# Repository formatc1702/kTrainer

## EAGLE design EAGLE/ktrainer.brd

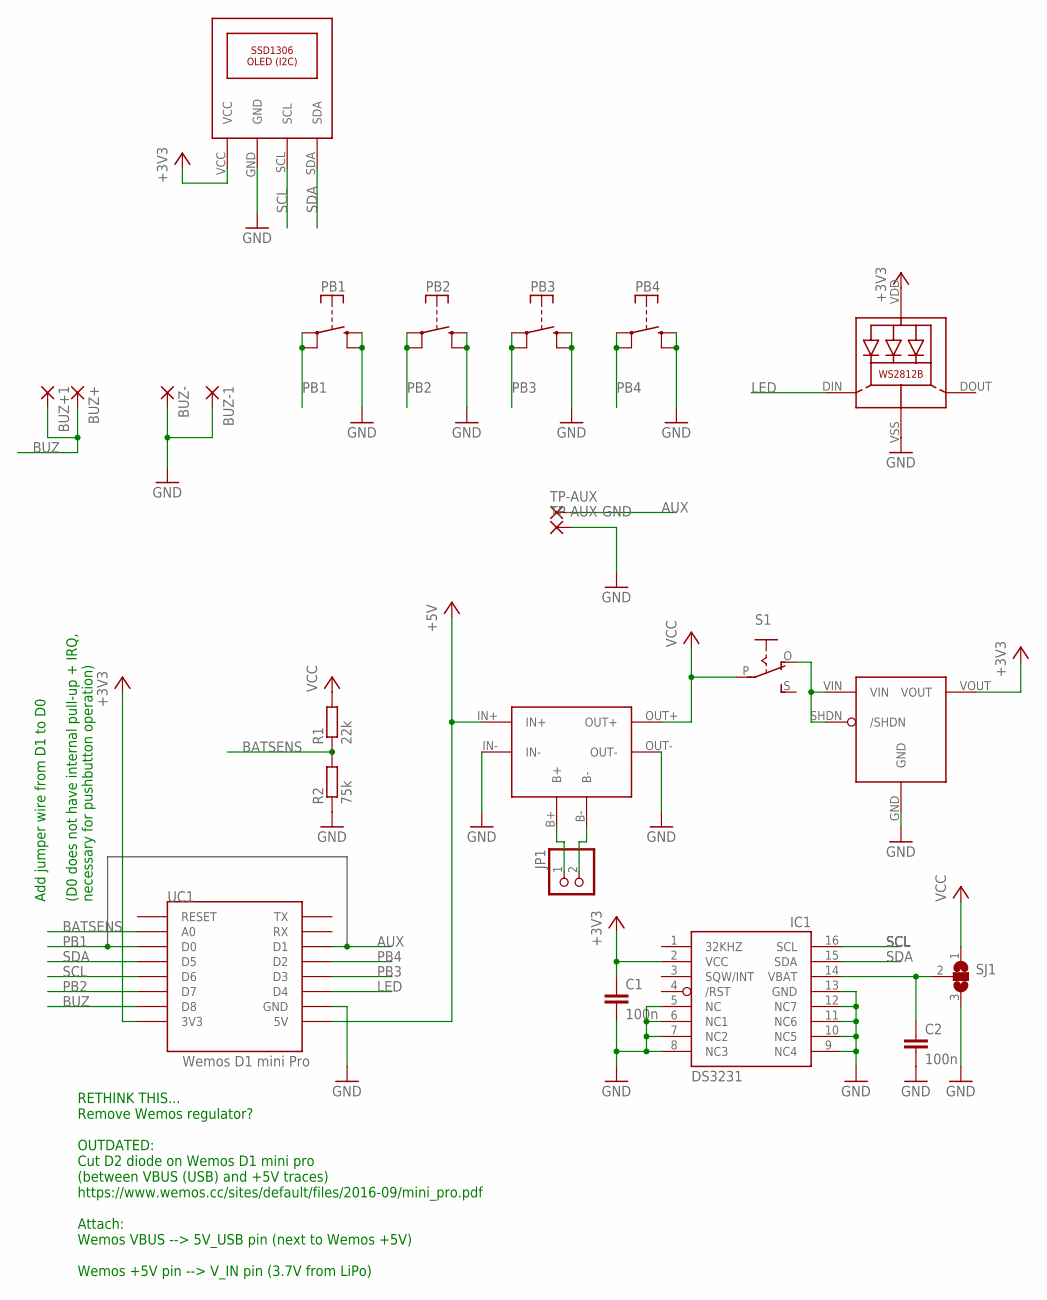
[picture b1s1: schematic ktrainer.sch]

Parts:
BUZ+, BUZ+1: SMD2; SMD1,27-2,54
BUZ-, BUZ-1: SMD2; SMD1,27-2,54
C1, C2: 100n; C0805
IC1: DS3231/SO; SO16W
JP1: PINHD-1X2; 1X02
LED1: WS2812B
PB1, PB2, PB3, PB4: SWITCH-SKRA; SWITCH-SKRA-PKG
R1: 22k; R0805
R2: 75k; R0805
S1: SWITCH-MSK12D04-SLIDER-SMD; SWITCH-MSK12D04-SLIDER-SMD-PKG
SJ1: SJ2W; SJ_2
TP-AUX: SMD2; SMD1,27-2,54
TP-AUX-GND: SMD2; SMD1,27-2,54
U$1: TP4056-LIPO-CHG-PCBTP4056-PCB-SMD; TP4056-PCB-SMD
U$2: SSD1306-OLED-128X64-I2CSSD1306-OLED-128X64-SMD; SSD1306-OLED-128X64-SMD
U$3: POLOLU-S7V8F3-3V3-STEP-UP-DOWNPOLOLU-S7V8F3-PAD; POLOLU-S7V8F3-SMD
UC1: Wemos D1 mini Pro; WEMOS-D1-MINI-SMD

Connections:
+3V3: C1.1, IC1.2 (VCC), LED1.VDD, U$2.VCC, U$3.VOUT, UC1.3V3
+5V: U$1.IN+, UC1.5V
AUX: TP-AUX.1, UC1.D1
B-: JP1.2, U$1.B-
BATSENS: R1.1, R2.2, UC1.A0
BUZ: BUZ+.1, BUZ+1.1, UC1.D8
GND: BUZ-.1, BUZ-1.1, C1.2, C2.2, IC1.5 (NC), IC1.6 (NC1), IC1.7 (NC2), IC1.8 (NC3), IC1.9 (NC4), IC1.10 (NC5), IC1.11 (NC6), IC1.12 (NC7), IC1.13 (GND), LED1.VSS (GND), PB1.P$1, PB1.P$2, PB2.P$1, PB2.P$2, PB3.P$1, PB3.P$2, PB4.P$1, PB4.P$2, R2.1, SJ1.3, TP-AUX-GND.1, U$1.IN-, U$1.OUT-, U$2.GND, U$3.GND, UC1.GND
LED: LED1.DIN (DI), UC1.D4
unnamed: S1.O, U$3.SHDN (/SHDN), U$3.VIN
PB1: PB1.P$3 (S), PB1.P$4 (S), UC1.D0
PB2: PB2.P$3 (S), PB2.P$4 (S), UC1.D7
PB3: PB3.P$3 (S), PB3.P$4 (S), UC1.D3
PB4: PB4.P$3 (S), PB4.P$4 (S), UC1.D2
SCL: IC1.16 (SCL), U$2.SCL, UC1.D6
SDA: IC1.15 (SDA), U$2.SDA, UC1.D5
VBAT: C2.1, IC1.14 (VBAT), SJ1.2
VCC: JP1.1, R1.2, S1.P, SJ1.1, U$1.B+, U$1.OUT+

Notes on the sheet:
RETHINK THIS... Remove Wemos regulator? OUTDATED: Cut D2 diode on Wemos D1 mini pro (between VBUS (USB) and +5V traces) https://www.wemos.cc/sites/default/files/2016-09/mini_pro.pdf Attach: Wemos VBUS --> 5V_USB pin (next to Wemos +5V) Wemos +5V pin --> V_IN pin (3.7V from LiPo)
Add jumper wire from D1 to D0 (D0 does not have internal pull-up + IRQ, necessary for pushbutton operation)

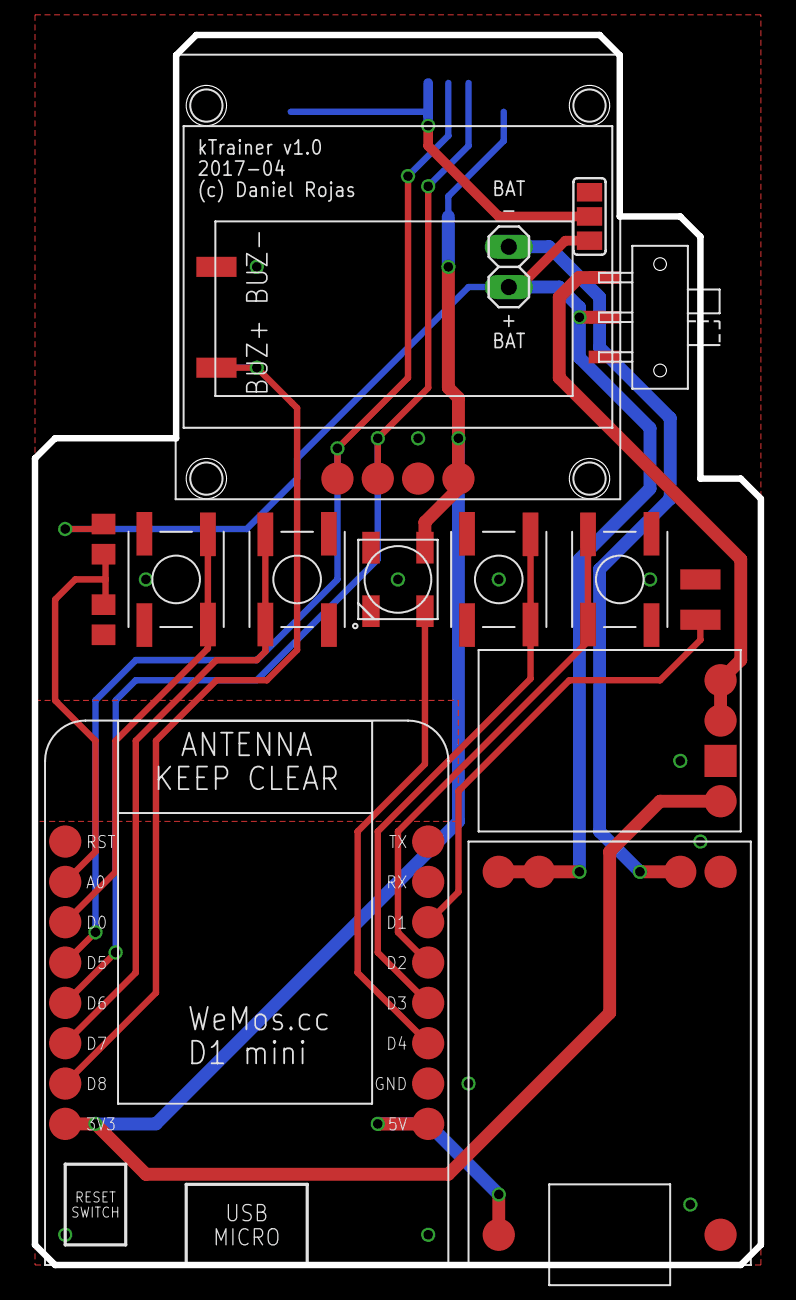
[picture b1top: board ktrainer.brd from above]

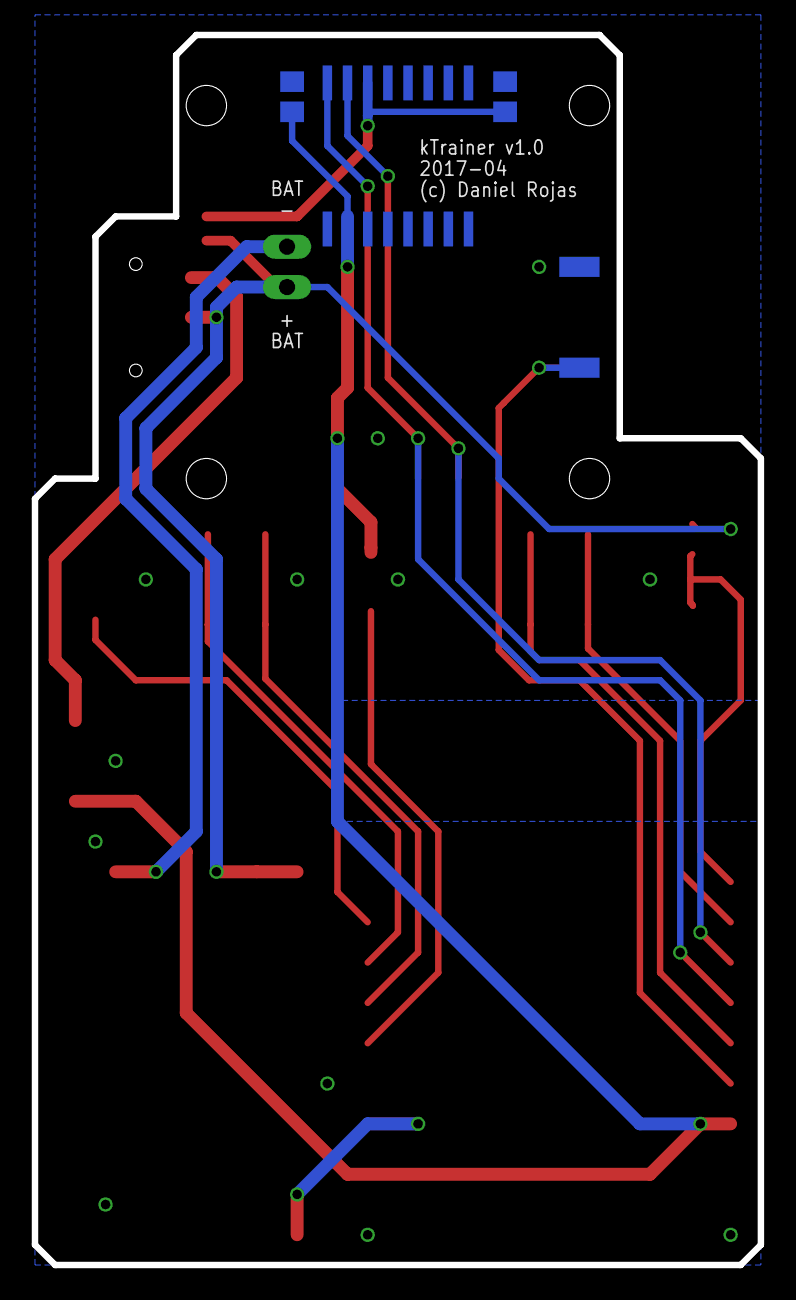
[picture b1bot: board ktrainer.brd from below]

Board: 2 copper layers, 45.7 x 77.5 mm, 23 parts (5 on the bottom side), 17 nets.

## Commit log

2017-02-16 First EAGLE tests
2017-02-16 Add Python state machine simulator test
2017-02-16 First debounce test
2017-02-24 Debug seems to work!
2017-02-25 Better debouncing, still needs diffferentiation between pressed/released
2017-02-25 Nice debouncing!
2017-02-26 Working state machine with 3 button control!
2017-02-26 Load/save file test works
2017-02-26 Save works upon startup, not after -> memory problem? implement load/save_training as part of kTraining class!
2017-02-27 Implement various changes
    De-clutter state machine
    implement load/save training into kTrain class
    add review mode
    fix bugs
2017-02-27 Remove blocking sleep() calls, implement skip/reset during countdown
2017-02-28 Some code cleanup
2017-03-05 Expand and adapt mpfshell script for Wemos D1 mini pro
2017-03-05 Add boot.py to disable WebREPL
2017-03-08 Implement minimalist working OLED interface
2017-03-09 Add Adafruit OLED Font library and implement variable font size
2017-03-10 Add simple bitmap binary file generator
2017-03-10 Use GUI icons
2017-03-10 Keep bitmap.bin always open
2017-03-10 Add some more icons
2017-03-10 Edit s_before… getting MemoryError!
2017-03-10 First thoughts on the physical layout of buttons & screen
2017-03-28 Work on schematic/PCB (not finished)
2017-04-14 More work on schematic/PCB (not finished)
2017-04-14 Make PCB fully SMD (only vias, no through-hole pads)
2017-04-14 Add mechanical CAD (not finished)
2017-04-15 Change to 128x64 OLED and rotate by 180 degrees
2017-04-17 Correct bitmapfont behavior with text size > 1
2017-04-17 Implement ktraindisp class (not finished)
2017-04-17 More PCB work
2017-04-17 Add helper script for mpfshell calls from Atom
2017-04-23 Finish work on PCB, create gerber files and order on Seeed Studio
2017-05-26 Add SolveSpace 3D CAD model
2017-05-26 Disable RGB LED at boot
    (because it's on the same pin as the on-board LED)
2017-05-26 Update code to match PCB pins
2017-05-26 Further 3D modeling (case top, USB, etc.)
2017-05-26 Detailing of 3D model
2017-05-26 Add standoffs to support PCB
2017-05-29 Add spacer between OLED and PCB
2017-05-29 Edit case bottom
2017-06-02 Temp
2017-06-02 Add rim to case top
2017-06-02 Test print bottom + slider
2017-06-02 Add geometry for buzzer (hole + pocket), print case bottom
2017-06-02 Model M1.6 Torx screws to hold top and bottom together
2017-06-02 Adjust geometry and print slider
2017-06-02 Adjust geometry and print case top
2017-06-02 Button test print
2017-06-02 Adjust geometry and print top case (2nd try)
2017-06-02 Adjust geometry and print OLED spacer
2017-06-02 Add photos of assembly process
2017-06-02 Adjust geometry and reprint buttons
2017-06-02 Adjust geometry and reprint case top (3rd try)
2017-06-03 Adjust geometry and reprint buttons (2nd and 3rd tries)
2017-06-03 Add simple firmware, similar to kTimer (LED only)
2017-06-03 Add 1mm of additional space for LiPo below PCB
2017-06-03 Implement non-blocking LED blinker
2017-06-03 Update training plan and parameters
2017-06-03 Annotate schematic: jumper wire from D1 to D0
2017-06-03 Adapt firmware to show four icons for four buttons
2017-06-03 Include buzzer (disabled for now)
2017-06-09 Convert LED hole to pocket (0.2mm wall thickness), since it's bright enough -> BREAKS main assembly!
2017-07-08 Update training plan
2017-07-08 Add notes for flashing firmware with esptool
2017-07-08 Change repetition counting to start from 1
2017-07-08 Archive some tests
2017-07-17 Make countdown and repetition counter more legible
2018-06-24 Upgrade to MicroPython 1.9.4
2018-06-24 Set resistor values for ADC voltage divider
2019-01-19 Rename old MicroPython folder, initialize PlatformIO project
2019-01-19 Start hardware definitions
2019-01-19 Add NeoPixel support
2019-01-19 Basic structure of training data
2019-01-19 more training functions
2019-01-19 Add State Machine library
2019-01-19 Basic state machine working
2019-03-30 prepare GUI framework
